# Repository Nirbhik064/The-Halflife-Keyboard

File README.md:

# The-Halflife-Keyboard.

Hey, so this is a custom mechanical keyboard designed by me with the help of a few guides over there on youtube.
I have fully designed the schematics by myself and also, have made the pcb for it.
I have tried to make it as a 65% keyboard with 68 keys and with leds under every key.

Here is the schematics image of the microcontroller, followed by the switch matrix and then the leds.

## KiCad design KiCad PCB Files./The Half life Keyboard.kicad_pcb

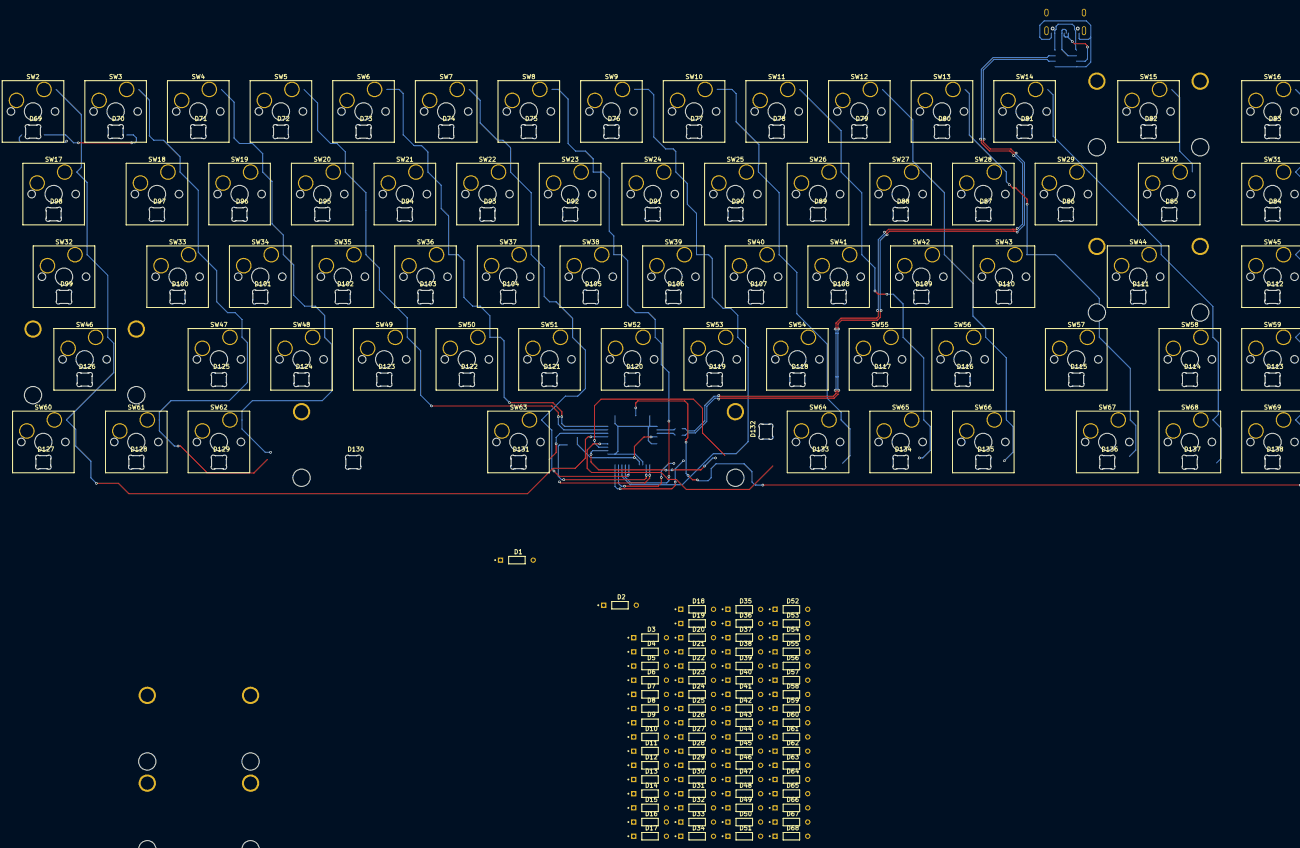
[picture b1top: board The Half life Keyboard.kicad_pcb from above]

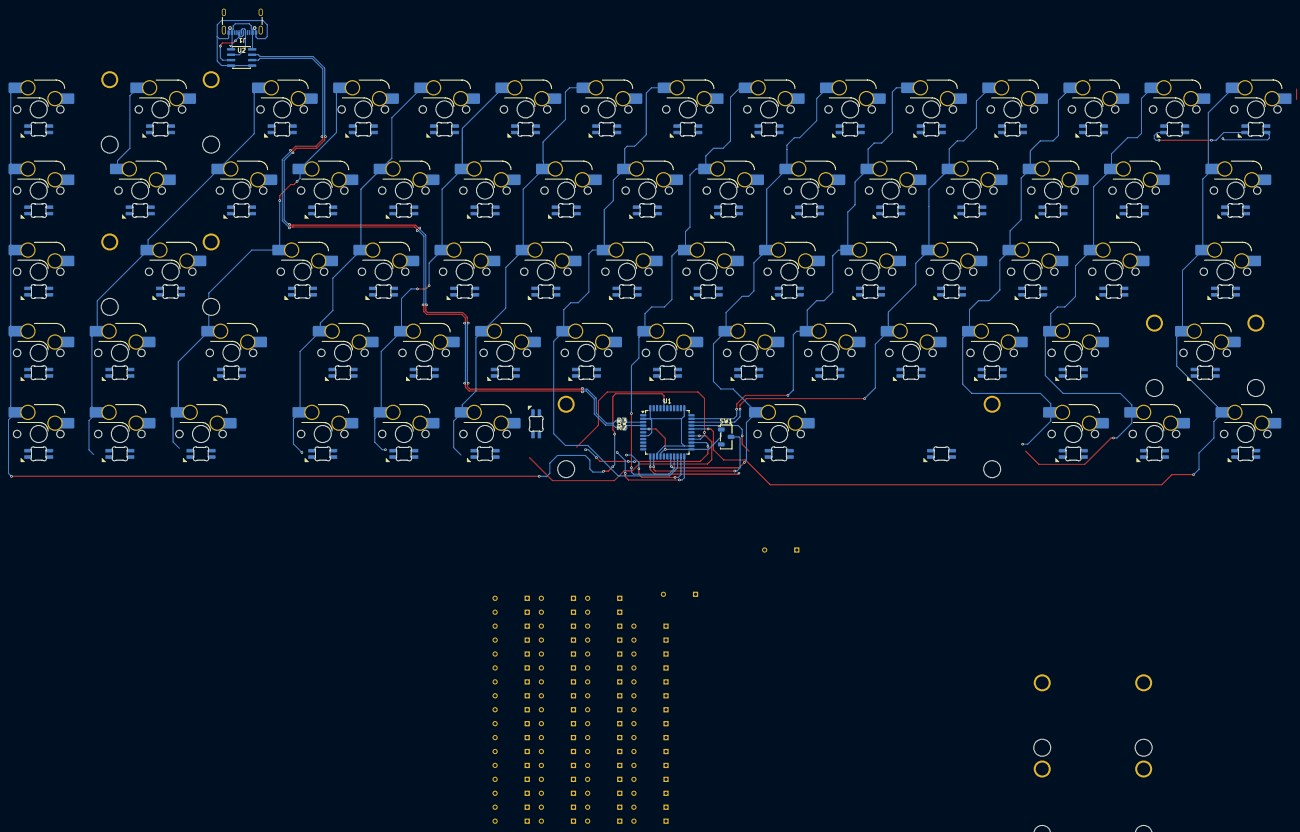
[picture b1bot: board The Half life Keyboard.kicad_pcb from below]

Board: 2 copper layers, 218 parts (6 on the bottom side), 94 nets.

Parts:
D1, D2, D3, D4, D5, D6, D7, D8, D9, D10, D11, D12, D13, D14, D15, D16, D17, D18, D19, D20, D21, D22, D23, D24, D25, D26, D27, D28, D29, D30, D31, D32, D33, D34, D35, D36, D37, D38, D39, D40, D41, D42, D43, D44, D45, D46, D47, D48, D49, D50, D51, D52, D53, D54, D55, D56, D57, D58, D59, D60, D61, D62, D63, D64, D65, D66, D67, D68: D; DIOAD753W49L380D172B
D69, D70, D71, D72, D73, D74, D75, D76, D77, D78, D79, D80, D81, D82, D83, D84, D85, D86, D87, D88, D89, D90, D91, D92, D93, D94, D95, D96, D97, D98, D99, D100, D101, D102, D103, D104, D105, D106, D107, D108, D109, D110, D111, D112, D113, D114, D115, D116, D117, D118, D119, D120, D121, D122, D123, D124, D125, D126, D127, D128, D129, D130, D131, D132, D133, D134, D135, D136, D137, D138: SK6812MINI-E; SK6812MINI-E_fixed
J1: USB_C_Receptacle_USB2.0_16P; USB_C_Receptacle_GCT_USB4105-xx-A_16P_TopMnt_Horizontal
R2, R3: 22 Ohm; RESC1608X55N
S1: MX_stab; STAB_MX_P_6.25u
S2, S2#2: MX_stab; STAB_MX_P_2u
S3, S3#2, S4: MX_stab; STAB_MX_P_2.25u
SW1: SW_Push; Nidec_Copal_CAS-120A
SW2, SW3, SW4, SW5, SW6, SW7, SW8, SW9, SW10, SW11, SW12, SW13, SW14, SW16, SW18, SW19, SW20, SW21, SW22, SW23, SW24, SW25, SW26, SW27, SW28, SW29, SW31, SW33, SW34, SW35, SW36, SW37, SW38, SW39, SW40, SW41, SW42, SW43, SW45, SW47, SW48, SW49, SW50, SW51, SW52, SW53, SW54, SW55, SW56, SW58, SW59, SW61, SW62, SW64, SW65, SW66, SW67, SW68, SW69: SW_Push; SW_Hotswap_Kailh_MX_Plated_1.00u
SW15: SW_Push; SW_Hotswap_Kailh_MX_Plated_2.00u
SW17, SW30: SW_Push; SW_Hotswap_Kailh_MX_Plated_1.50u
SW32, SW57: SW_Push; SW_Hotswap_Kailh_MX_Plated_1.75u
SW44, SW46: SW_Push; SW_Hotswap_Kailh_MX_Plated_2.25u
SW60: SW_Push; SW_Hotswap_Kailh_MX_Plated_1.25u
SW63: SW_Push; SW_Hotswap_Kailh_MX_Plated_6.25u
U1: ATmega32U4-A; TQFP-44_10x10mm_P0.8mm
U2: USB6B1; SOIC-8_3.9x4.9mm_P1.27mm

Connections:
C0: SW2.2, SW17.2, SW32.2, SW46.2, SW60.2, U1.29 (PB5)
C1: SW3.2, SW18.2, SW33.2, SW47.2, SW61.2, U1.30 (PB6)
C2: SW4.2, SW19.2, SW34.2, SW48.2, SW62.2, U1.12 (PB7)
C3: SW5.2, SW20.2, SW35.2, SW49.2, U1.31 (PC6)
C4: SW6.2, SW21.2, SW36.2, SW50.2, U1.32 (PC7)
C5: SW7.2, SW22.2, SW37.2, SW51.2, SW63.2, U1.18 (PD0)
C6: SW8.2, SW23.2, SW38.2, SW52.2, U1.19 (PD1)
C7: SW9.2, SW24.2, SW39.2, SW53.2, U1.20 (PD2)
C8: SW10.2, SW25.2, SW40.2, SW54.2, SW64.2, U1.21 (PD3)
C9: SW11.2, SW26.2, SW41.2, SW55.2, SW65.2, U1.25 (PD4)
C10: SW12.2, SW27.2, SW42.2, SW56.2, SW66.2, U1.22 (PD5)
C11: SW13.2, SW28.2, SW43.2, SW57.2, SW67.2, U1.26 (PD6)
C12: SW14.2, SW29.2, SW44.2, SW58.2, SW68.2, U1.27 (PD7)
C13: SW15.2, SW30.2, U1.41 (PF0)
C14: SW16.2, SW31.2, SW45.2, SW59.2, SW69.2, U1.40 (PF1)
D+: R2.1, U2.6 (I/O2)
D-: R3.2, U2.7 (I/O1)
GND: D69.3 (VSS), D70.3 (VSS), D71.3 (VSS), D72.3 (VSS), D73.3 (VSS), D74.3 (VSS), D75.3 (VSS), D76.3 (VSS), D77.3 (VSS), D78.3 (VSS), D79.3 (VSS), D80.3 (VSS), D81.3 (VSS), D82.3 (VSS), D83.3 (VSS), D84.3 (VSS), D85.3 (VSS), D86.3 (VSS), D87.3 (VSS), D88.3 (VSS), D89.3 (VSS), D90.3 (VSS), D91.3 (VSS), D92.3 (VSS), D93.3 (VSS), D94.3 (VSS), D95.3 (VSS), D96.3 (VSS), D97.3 (VSS), D98.3 (VSS), D99.3 (VSS), D100.3 (VSS), D101.3 (VSS), D102.3 (VSS), D103.3 (VSS), D104.3 (VSS), D105.3 (VSS), D106.3 (VSS), D107.3 (VSS), D108.3 (VSS), D109.3 (VSS), D110.3 (VSS), D111.3 (VSS), D112.3 (VSS), D113.3 (VSS), D114.3 (VSS), D115.3 (VSS), D116.3 (VSS), D117.3 (VSS), D118.3 (VSS), D119.3 (VSS), D120.3 (VSS), D121.3 (VSS), D122.3 (VSS), D123.3 (VSS), D124.3 (VSS), D125.3 (VSS), D126.3 (VSS), D127.3 (VSS), D128.3 (VSS), D129.3 (VSS), D130.3 (VSS), D131.3 (VSS), D132.3 (VSS), D133.3 (VSS), D134.3 (VSS), D135.3 (VSS), D136.3 (VSS), D137.3 (VSS), D138.3 (VSS), J1.A1 (GND), J1.A12 (GND), J1.B1 (GND), J1.B12 (GND), SW1.1, U1.5 (UGND), U1.15 (GND), U1.23 (GND), U1.35 (GND), U1.43 (GND), U2.4 (GND), U2.5 (GND)
LEDS Input: D69.4 (DIN), U1.39 (PF4)
unnamed: D69.2 (DOUT), D70.4 (DIN)
unnamed: D70.2 (DOUT), D71.4 (DIN)
unnamed: D71.2 (DOUT), D72.4 (DIN)
unnamed: D72.2 (DOUT), D73.4 (DIN)
unnamed: D73.2 (DOUT), D74.4 (DIN)
unnamed: D74.2 (DOUT), D75.4 (DIN)
unnamed: D75.2 (DOUT), D76.4 (DIN)
unnamed: D76.2 (DOUT), D77.4 (DIN)
unnamed: D77.2 (DOUT), D78.4 (DIN)
unnamed: D78.2 (DOUT), D79.4 (DIN)
unnamed: D79.2 (DOUT), D80.4 (DIN)
unnamed: D80.2 (DOUT), D81.4 (DIN)
unnamed: D81.2 (DOUT), D82.4 (DIN)
unnamed: D82.2 (DOUT), D83.4 (DIN)
unnamed: D83.2 (DOUT), D84.4 (DIN)
unnamed: D84.2 (DOUT), D85.4 (DIN)
unnamed: D85.2 (DOUT), D86.4 (DIN)
unnamed: D86.2 (DOUT), D87.4 (DIN)
unnamed: D87.2 (DOUT), D88.4 (DIN)
unnamed: D88.2 (DOUT), D89.4 (DIN)
unnamed: D89.2 (DOUT), D90.4 (DIN)
unnamed: D90.2 (DOUT), D91.4 (DIN)
unnamed: D91.2 (DOUT), D92.4 (DIN)
unnamed: D92.2 (DOUT), D93.4 (DIN)
unnamed: D93.2 (DOUT), D94.4 (DIN)
unnamed: D94.2 (DOUT), D95.4 (DIN)
unnamed: D95.2 (DOUT), D96.4 (DIN)
unnamed: D96.2 (DOUT), D97.4 (DIN)
unnamed: D97.2 (DOUT), D98.4 (DIN)
unnamed: D98.2 (DOUT), D99.4 (DIN)
unnamed: D99.2 (DOUT), D100.4 (DIN)
unnamed: D100.2 (DOUT), D101.4 (DIN)
unnamed: D101.2 (DOUT), D102.4 (DIN)
unnamed: D102.2 (DOUT), D103.4 (DIN)
unnamed: D103.2 (DOUT), D104.4 (DIN)
unnamed: D104.2 (DOUT), D105.4 (DIN)
unnamed: D105.2 (DOUT), D106.4 (DIN)
unnamed: D106.2 (DOUT), D107.4 (DIN)
unnamed: D107.2 (DOUT), D108.4 (DIN)
unnamed: D108.2 (DOUT), D109.4 (DIN)
unnamed: D109.2 (DOUT), D110.4 (DIN)
unnamed: D110.2 (DOUT), D111.4 (DIN)
unnamed: D111.2 (DOUT), D112.4 (DIN)
unnamed: D112.2 (DOUT), D113.4 (DIN)
unnamed: D113.2 (DOUT), D114.4 (DIN)
unnamed: D114.2 (DOUT), D115.4 (DIN)
unnamed: D115.2 (DOUT), D116.4 (DIN)
unnamed: D116.2 (DOUT), D117.4 (DIN)
unnamed: D117.2 (DOUT), D118.4 (DIN)
unnamed: D118.2 (DOUT), D119.4 (DIN)
unnamed: D119.2 (DOUT), D120.4 (DIN)
unnamed: D120.2 (DOUT), D121.4 (DIN)
unnamed: D121.2 (DOUT), D122.4 (DIN)
unnamed: D122.2 (DOUT), D123.4 (DIN)
unnamed: D123.2 (DOUT), D124.4 (DIN)
unnamed: D124.2 (DOUT), D125.4 (DIN)
unnamed: D125.2 (DOUT), D126.4 (DIN)
unnamed: D126.2 (DOUT), D127.4 (DIN)
unnamed: D127.2 (DOUT), D128.4 (DIN)
unnamed: D128.2 (DOUT), D129.4 (DIN)
unnamed: D129.2 (DOUT), D130.4 (DIN)
unnamed: D130.2 (DOUT), D131.4 (DIN)
unnamed: D131.2 (DOUT), D132.4 (DIN)
unnamed: D132.2 (DOUT), D133.4 (DIN)
unnamed: D133.2 (DOUT), D134.4 (DIN)
unnamed: D134.2 (DOUT), D135.4 (DIN)
unnamed: D135.2 (DOUT), D136.4 (DIN)
unnamed: D136.2 (DOUT), D137.4 (DIN)
unnamed: D137.2 (DOUT), D138.4 (DIN)
unnamed: J1.A6 (D+), J1.B6 (D+), U2.3 (I/O2)
unnamed: J1.A7 (D-), J1.B7 (D-), U2.2 (I/O1)
unnamed: R2.2, U1.4 (D+)
unnamed: R3.1, U1.3 (D-)
unnamed: SW1.2, U1.13 (~RESET)
VBUS: D69.1 (VDD), D70.1 (VDD), D71.1 (VDD), D72.1 (VDD), D73.1 (VDD), D74.1 (VDD), D75.1 (VDD), D76.1 (VDD), D77.1 (VDD), D78.1 (VDD), D79.1 (VDD), D80.1 (VDD), D81.1 (VDD), D82.1 (VDD), D83.1 (VDD), D84.1 (VDD), D85.1 (VDD), D86.1 (VDD), D87.1 (VDD), D88.1 (VDD), D89.1 (VDD), D90.1 (VDD), D91.1 (VDD), D92.1 (VDD), D93.1 (VDD), D94.1 (VDD), D95.1 (VDD), D96.1 (VDD), D97.1 (VDD), D98.1 (VDD), D99.1 (VDD), D100.1 (VDD), D101.1 (VDD), D102.1 (VDD), D103.1 (VDD), D104.1 (VDD), D105.1 (VDD), D106.1 (VDD), D107.1 (VDD), D108.1 (VDD), D109.1 (VDD), D110.1 (VDD), D111.1 (VDD), D112.1 (VDD), D113.1 (VDD), D114.1 (VDD), D115.1 (VDD), D116.1 (VDD), D117.1 (VDD), D118.1 (VDD), D119.1 (VDD), D120.1 (VDD), D121.1 (VDD), D122.1 (VDD), D123.1 (VDD), D124.1 (VDD), D125.1 (VDD), D126.1 (VDD), D127.1 (VDD), D128.1 (VDD), D129.1 (VDD), D130.1 (VDD), D131.1 (VDD), D132.1 (VDD), D133.1 (VDD), D134.1 (VDD), D135.1 (VDD), D136.1 (VDD), D137.1 (VDD), D138.1 (VDD), J1.A4 (VBUS), J1.A9 (VBUS), J1.B4 (VBUS), J1.B9 (VBUS), U1.2 (UVCC), U1.7 (VBUS), U1.14 (VCC), U1.24 (AVCC), U1.34 (VCC), U1.44 (AVCC), U2.1 (VBUS), U2.8 (VBUS)
